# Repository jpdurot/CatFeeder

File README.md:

# CatFeeder

This repository contains all source code from my pet project.
This project is composed of many DIY elements :
 - The cat feeder itself, essentially made of woods and plastic
 - Electronics (micro controllers, servo, sensors, ...), with home made circuits and PCB
 - Microcontroller development (Atmel 8 bits)
 - Hybrid mobile app to control micro controllers (Cordova, Ionic2, Angular2)
 
## Releases
No release yet, look at issues for what is remaining before 1.0 version

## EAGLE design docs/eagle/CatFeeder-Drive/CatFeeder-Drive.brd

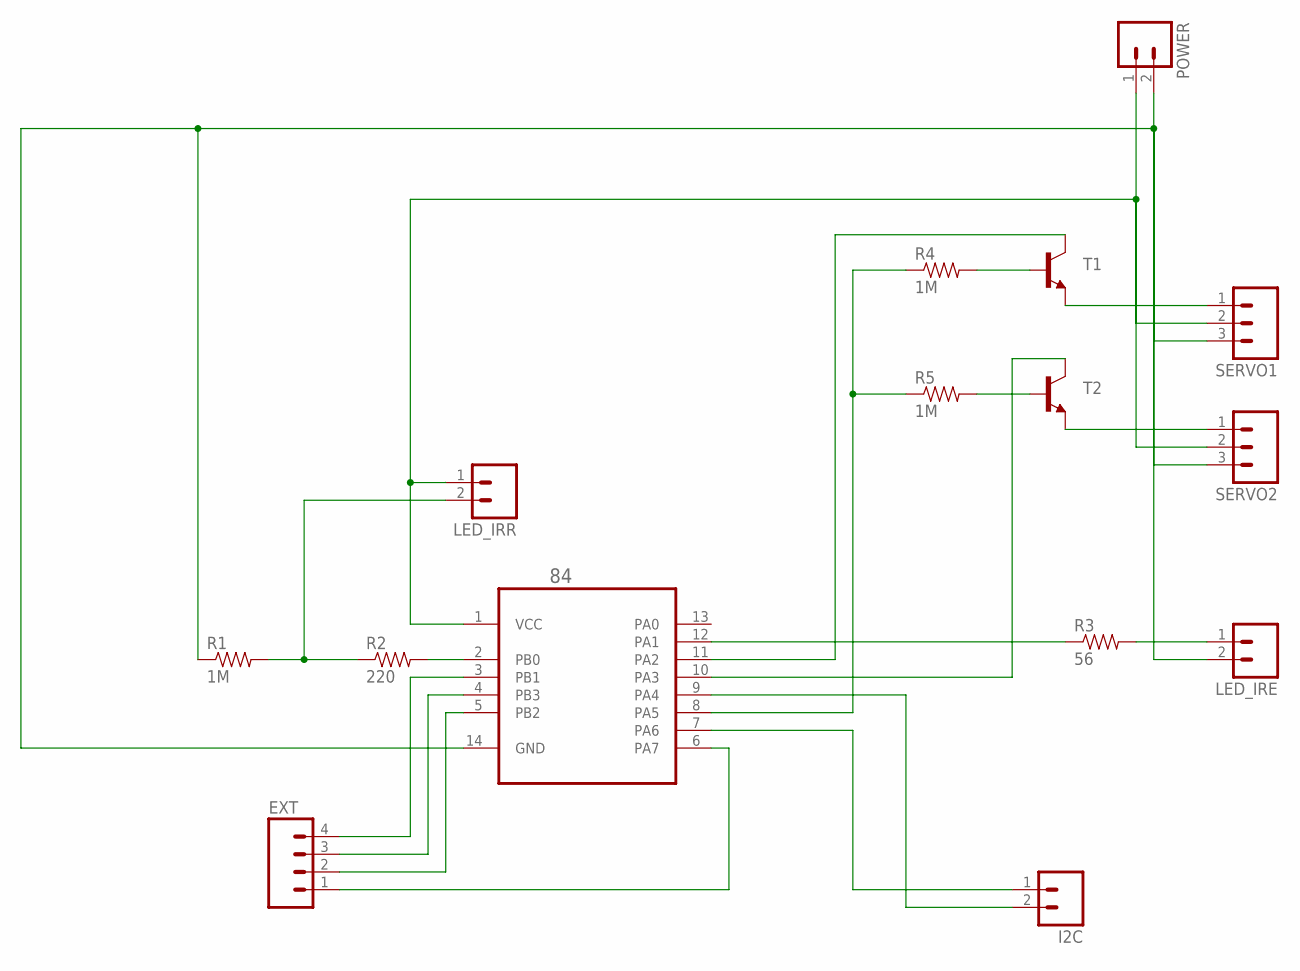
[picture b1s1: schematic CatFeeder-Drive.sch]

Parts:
84: ATTINY84-20PU; DIP254P762X533-14
EXT: M041X04_NO_SILK; 1X04_NO_SILK
I2C: M02PTH; 1X02
LED_IRE: M02LOCK; 1X02_LOCK
LED_IRR: M02LOCK; 1X02_LOCK
POWER: M02LOCK; 1X02_LOCK
R1, R4, R5: 1M; AXIAL-0.4
R2: 220; AXIAL-0.4
R3: 56; AXIAL-0.4
SERVO1, SERVO2: M031X03_NO_SILK; 1X03_NO_SILK
T1, T2: TRANSISTOR_NPNBC547; TO-92-AMMO

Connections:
$N$8: 84.11 (PA2), T1.1 (C)
LED_IRR: 84.1 (VCC), LED_IRR.1, POWER.1, SERVO1.2, SERVO2.2
unnamed: 84.9 (PA4), I2C.2
unnamed: 84.7 (PA6), I2C.1
unnamed: 84.8 (PA5), R4.P$1 (1), R5.P$1 (1)
unnamed: R4.P$2 (2), T1.2 (B)
unnamed: R5.P$2 (2), T2.2 (B)
unnamed: 84.3 (PB1), EXT.4
unnamed: 84.10 (PA3), T2.1 (C)
unnamed: SERVO1.1, T1.3 (E)
unnamed: SERVO2.1, T2.3 (E)
unnamed: 84.2 (PB0), R2.P$2 (2)
unnamed: 84.12 (PA1), R3.P$1 (1)
unnamed: 84.4 (PB3), EXT.3
unnamed: LED_IRE.1, R3.P$2 (2)
unnamed: 84.5 (PB2), EXT.2
unnamed: LED_IRR.2, R1.P$2 (2), R2.P$1 (1)
unnamed: 84.14 (GND), LED_IRE.2, POWER.2, R1.P$1 (1), SERVO1.3, SERVO2.3
unnamed: 84.6 (PA7), EXT.1

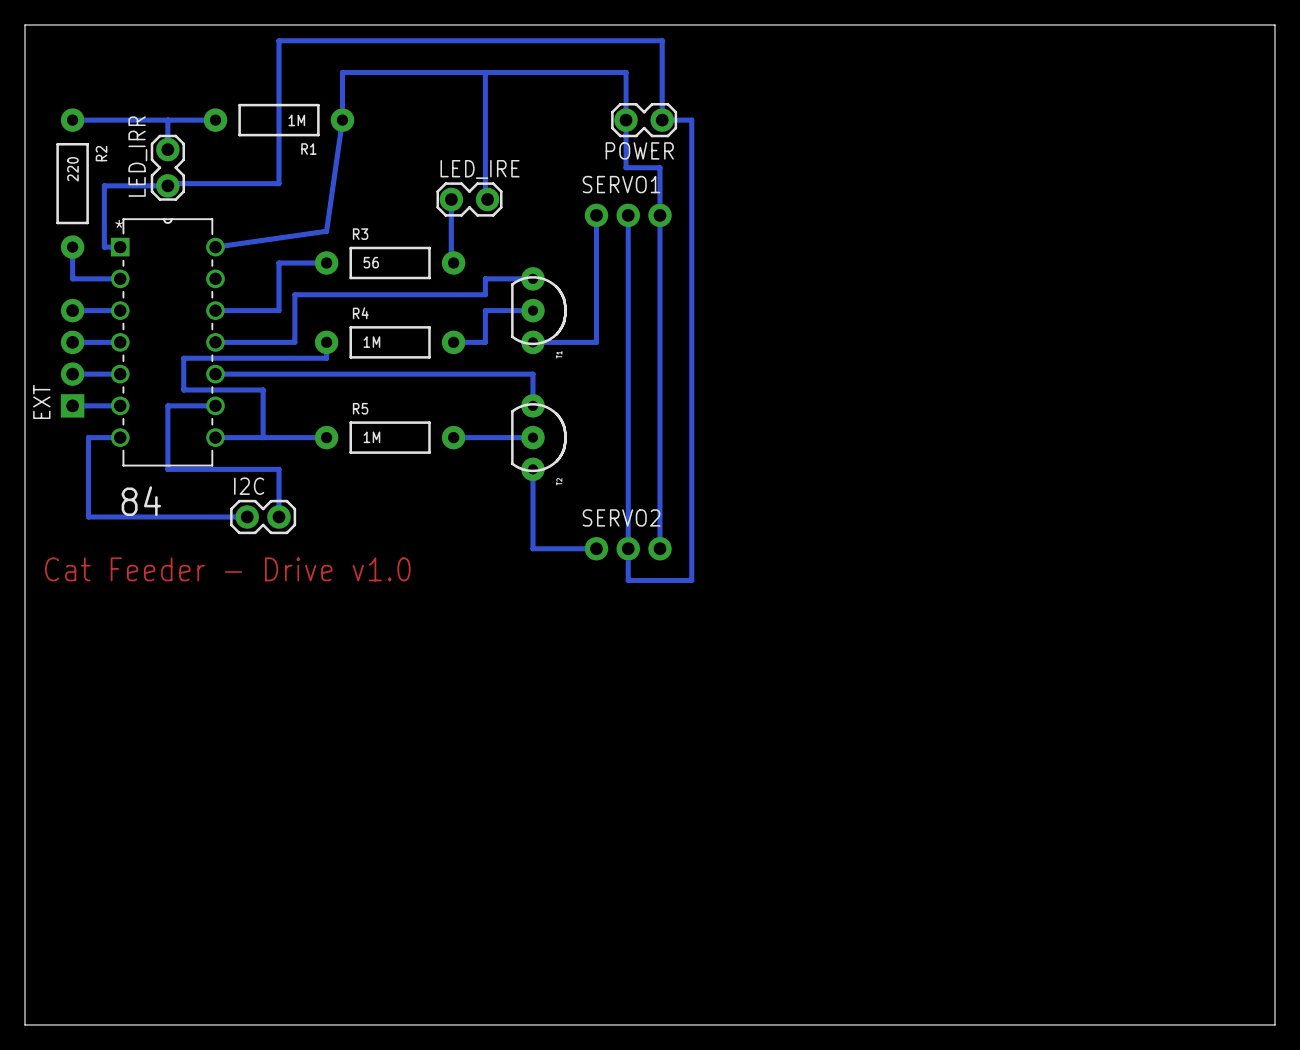
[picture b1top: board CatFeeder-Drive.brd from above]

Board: 2 copper layers, 100.0 x 80.0 mm, 15 parts (0 on the bottom side), 19 nets.

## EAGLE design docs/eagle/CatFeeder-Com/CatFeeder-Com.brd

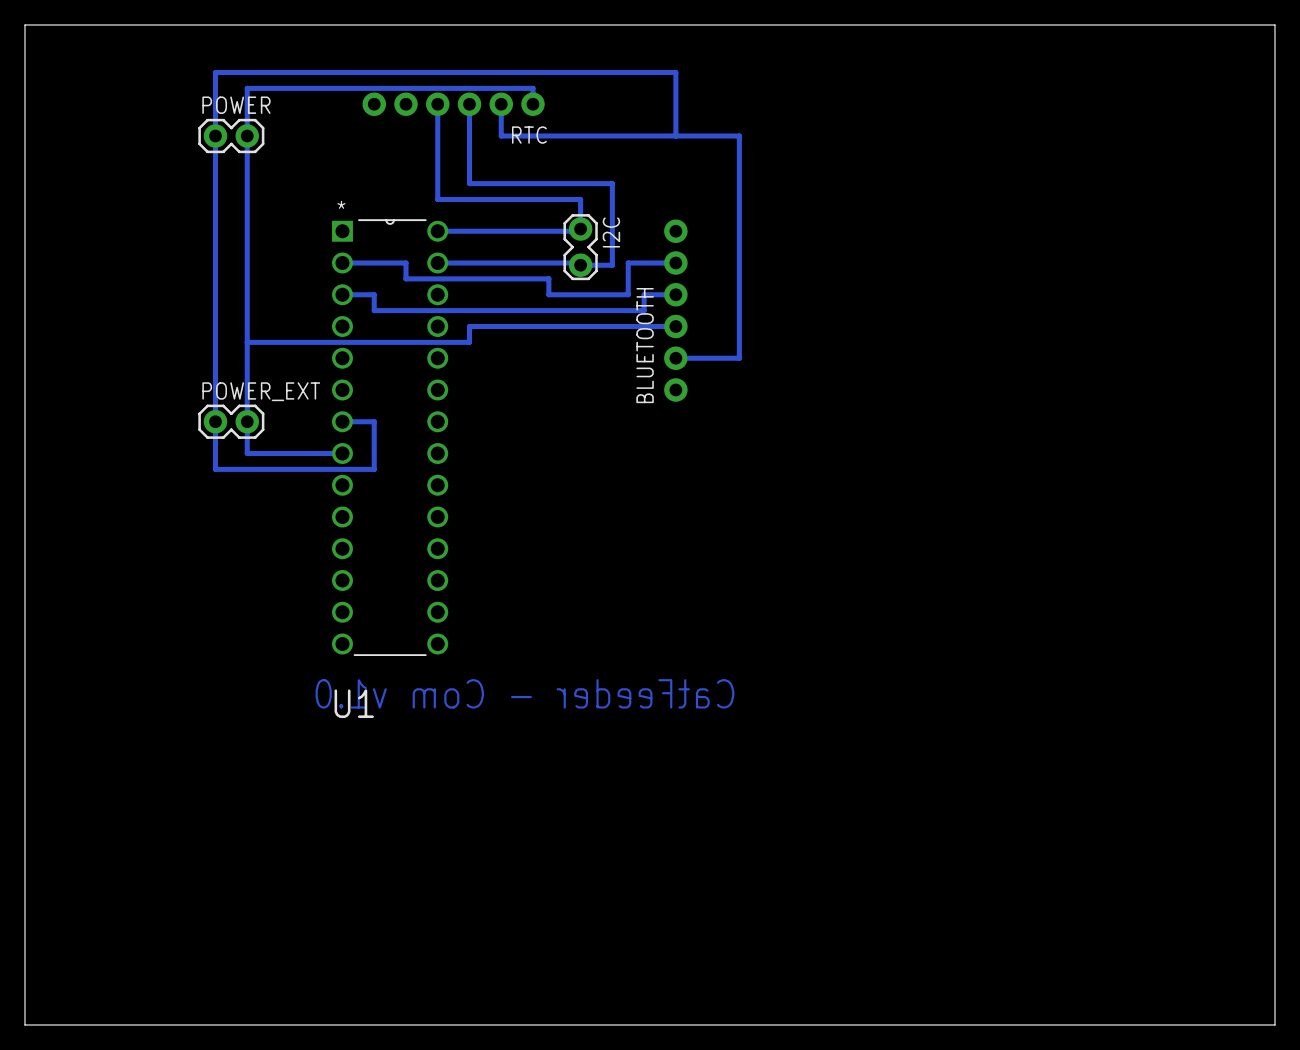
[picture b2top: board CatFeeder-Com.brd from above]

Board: 2 copper layers, 100.0 x 80.0 mm, 6 parts (0 on the bottom side), 6 nets.

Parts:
BLUETOOTH: 1X06_NO_SILK
I2C: 1X02_LOCK
POWER: 1X02
POWER_EXT: 1X02
RTC: 1X06_NO_SILK
U1: ATMEGA328P-PU; DIP254P762X457-28

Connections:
I2C: BLUETOOTH.2, POWER.1, POWER_EXT.1, RTC.2, U1.7
unnamed: BLUETOOTH.5, U1.2
unnamed: BLUETOOTH.4, U1.3
unnamed: I2C.1, RTC.4, U1.28
unnamed: BLUETOOTH.3, POWER.2, POWER_EXT.2, RTC.1, U1.8
unnamed: I2C.2, RTC.3, U1.27

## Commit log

2016-01-05 Added Eagle schematics and board for CatFeeder-Drive board
2016-01-05 Added post build event
2016-01-05 Refactoring on message handling system
2016-01-05 Create app skeleton based on Cordova and AngularJS 2
2016-01-07 Integration of Angular 2 Router + First view
2016-01-07 Ignore JS source map files
2016-01-08 Added Gulp workflow to build app (TS, SASS, live server, ...)
2016-01-08 Fixed router configuration
2016-01-08 Ignore JS files and sourcemaps files inside app directory
2016-01-10 Remove gulp-debug from file
2016-01-10 Fix TS warning
2016-01-10 Re-add accidentally deleted file
2016-01-10 Added bluetooth plugin
2016-01-17 Ionic 2 application initial commit
2016-01-17 Added base screens + bluetooth plugin
2016-01-17 Fix THIS usage inside callback
2016-01-18 Added info on bluetooth connection
2016-01-18 Beginning of bluetooth service implementation
2016-01-19 Added custom pipe for bluetooth status display
2016-01-19 Bluetooth service first implementation and usage
2016-01-19 Remove default device name
2016-01-19 Settings persistence in local storage
2016-01-19 Don't connect everytime we come back to the app page
2016-01-19 Display found device in console
2016-01-19 Simple event handling system
2016-01-20 Simplify imports with namespaces
2016-01-20 Beginning of data reception and messaging system
2016-01-20 Refacto
2016-01-20 Remove renamed file
2016-01-20 Register services at App level and inject them in constructors
2016-01-20 Send message implementation (To be tested)
2016-01-28 Removed all debug string messages sent by serial port
2016-02-14 Handle bluetooth messages from mobile app
2016-02-24 Added logger service and UI logs
2016-02-24 Packets and responses are now in binary format
2016-02-24 Code clean up
2016-09-05 Add first version
2016-09-05 Remove temp files
2017-04-12 Migration from AVR studio to PlatformIO
2018-01-04 Rename I2C slave library files
2018-01-04 Driver implementation
2018-01-04 Weight management using HX711 driver
2018-01-04 Complete refactoring to handle weight sensor
2018-01-04 Renaming
2018-01-04 Remove Atmel Studio related stuff
2018-01-26 Remove debug stats on I2C
2018-01-26 Move servo to correct initial position before starting feeding
2018-01-26 Set slave id method renaming
2018-01-29 Food weight is now configurable in a I2C register
2018-02-09 Convert into platform io project
2018-02-09 Add AT commands management
2018-02-09 Init serial bus from global init method
2018-02-09 Add method to write integer value in a string form
2018-02-09 Ability to convert a string to int with error checking
2018-02-09 Add calibration AT command
2018-08-12 Add Feed command
2018-08-12 Add FEEDER_TEST flag to allow adjustements without weight sensor
2018-10-02 Remove TEST mode
2018-10-02 Remove unused file
2018-10-02 Remove old mobile application
2018-10-02 Initial commit for NEW mobile version
2018-10-03 Change app icon
2018-10-03 Allow only one alert at once, and don't poll server when alert is displayed
2018-10-03 Initial commit of the Web API
2018-10-04 Add settings persistence
2018-10-04 Add settings data file to ignore list
2018-10-04 Convert CJS to EcmaScript modules :)
2018-10-08 Add minimal scheduler
2018-10-08 Fix bug when reading settings
2018-10-10 Add API to get current schedules
2018-10-11 Add history and persistence on last feeds information
2018-10-11 Fix get infos API, where last feed value was always empty...
2018-10-13 Change application general information
2018-10-13 Add API to retrieve all feeds of last 7 days
2018-11-03 Add history screen with last 7 days feeds
2018-11-03 Fix missing translations
2018-11-04 Date pipe is now i18n compliant
2018-11-04 Sign generated apk

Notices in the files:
parts and their libraries:
SparkFun-Connectors: Licensing: Creative Commons ShareAlike 4.0 International - https://creativecommons.org/licenses/by-sa/4.0
